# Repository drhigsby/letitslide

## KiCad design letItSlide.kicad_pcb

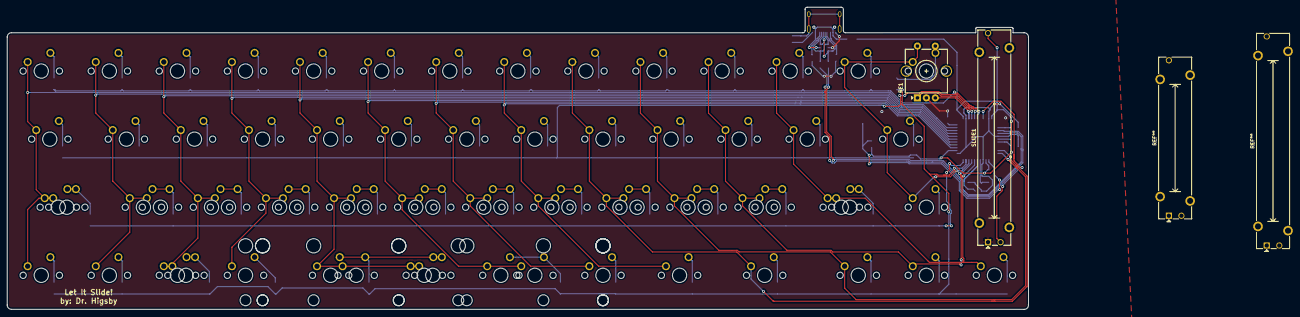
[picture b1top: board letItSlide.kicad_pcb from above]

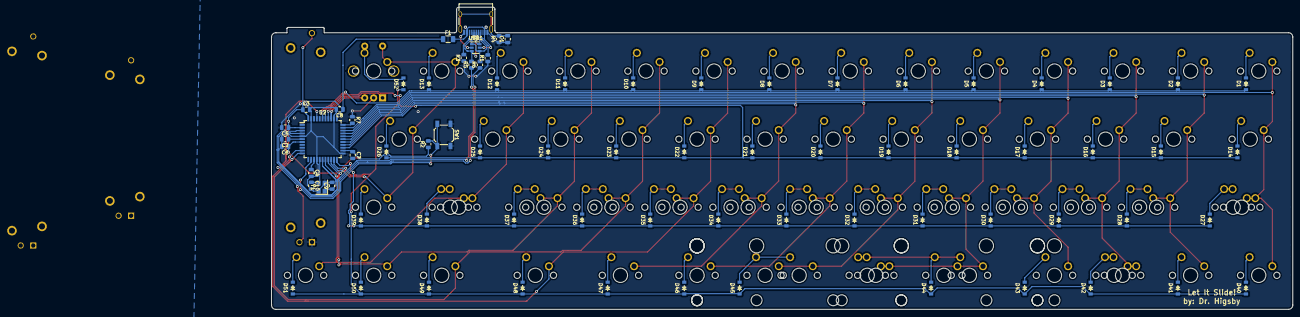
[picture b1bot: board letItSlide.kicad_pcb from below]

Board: 2 copper layers, 285.8 x 84.5 mm, 146 parts (75 on the bottom side), 87 nets.

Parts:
C1: 4.7n; C_0805_2012Metric
C2: 1uF; C_0805_2012Metric
C3, C4, C5, C6, C7: 0.1uF; C_0805_2012Metric
C8: 10uF; C_0805_2012Metric
C9, C10: 22; C_0805_2012Metric
D1, D2, D3, D4, D5, D6, D7, D8, D9, D10, D11, D12, D13, D14, D15, D16, D17, D18, D19, D20, D21, D22, D23, D24, D25, D26, D27, D28, D29, D30, D31, D32, D33, D34, D35, D36, D37, D38, D39, D40, D41, D42, D43, D44, D45, D46, D47, D48, D49, D50, D51, D52: D_Small; D_SOD-123
F1: 500 mA; Fuse_1206_3216Metric
MX1, MX2, MX3, MX4, MX5, MX6, MX7, MX8, MX9, MX10, MX11, MX12, MX13, MX15, MX16, MX17, MX18, MX19, MX20, MX21, MX22, MX23, MX24, MX25, MX28, MX28#2, MX29, MX29#2, MX30, MX30#2, MX31, MX31#2, MX32, MX32#2, MX33, MX33#2, MX34, MX34#2, MX35, MX35#2, MX36, MX36#2, MX37, MX37#2, MX39, MX40, MX41, MX42, MX43, MX46, MX49, MX50, MX51, MX52: MX-NoLED; MXOnly-1U-NoLED
MX14, MX38-1.25u1, MX42-1.25u1, MX47, MX48: MX-NoLED; MXOnly-1.25U-NoLED
MX26, MX27-1.75u1: MX-NoLED; MXOnly-1.75U-NoLED
MX27, MX38: MX-NoLED; MXOnly-1.5U-NoLED
MX44: MX-NoLED; MXOnly-2.25U-ReversedStabilizers-NoLED
MX44-3u1, MX45-3u1: MX-NoLED; MXOnly-3U-ReversedStabilizers-NoLED
MX44-6.25u1: MX-NoLED; MXOnly-6.25U-ReversedStabilizers-NoLED
MX44-6u1: MX-NoLED; MXOnly-6U-Centered-ReversedStabilizers-NoLED
MX45: MX-NoLED; MXOnly-2U-ReversedStabilizers-NoLED
R1, R3: 5.1k; R_0805_2012Metric
R2, R7: 10k; R_0805_2012Metric
R4: 1M; R_0805_2012Metric
R5, R6: 22; R_0805_2012Metric
RE1: Rotary_Encoder_Switch; RotaryEncoder_Alps_EC11E-Switch_Vertical_H20mm_CircularMoun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
SLIDE1: Conn_01x07_Male; Potentiometer_Bourns_PTA4543_Single_Slide
SW1: SW_Push; SW_SPST_SKQG_WithStem
U1: SRV05-4; SOT-23-6
U2: ATmega32U4-AU; TQFP-44_10x10mm_P0.8mm
USB1: USB_C_Receptacle_USB2.0; USB_C_Receptacle_HRO_TYPE-C-31-M-12
Y1: Crystal_GND24_Small; Crystal_SMD_3225-4Pin_3.2x2.5mm

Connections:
+5V: C3.1, C4.1, C5.1, C6.1, C7.1, C8.1, F1.1, R2.1, SLIDE1.3, U2.2, U2.7, U2.14, U2.24, U2.34, U2.44
ANAL_IN: SLIDE1.2, U2.41
D+: R5.2, U1.3, U1.6, USB1.A6, USB1.B6
D-: R6.2, U1.1, U1.4, USB1.A7, USB1.B7
Earth: C1.2, R4.2, USB1.S1
GND: C1.1, C2.2, C3.2, C4.2, C5.2, C6.2, C7.2, C8.2, C9.2, C10.2, R1.1, R3.1, R4.1, R7.1, RE1.C, SLIDE1.1, SW1.1, U1.2, U2.5, U2.15, U2.23, U2.35, U2.43, USB1.A1, USB1.A12, USB1.B1, USB1.B12, Y1.2, Y1.4
MG1: RE1.B, U2.36
MG2: RE1.A, U2.37
unnamed: C2.1, U2.6
unnamed: C9.1, U2.17, Y1.1
unnamed: C10.1, U2.16, Y1.3
unnamed: D1.2, MX1.2
unnamed: D2.2, MX2.2
unnamed: D3.2, MX3.2
unnamed: D4.2, MX4.2
unnamed: D5.2, MX5.2
unnamed: D6.2, MX6.2
unnamed: D7.2, MX7.2
unnamed: D8.2, MX8.2
unnamed: D9.2, MX9.2
unnamed: D10.2, MX10.2
unnamed: D11.2, MX11.2
unnamed: D12.2, MX12.2
unnamed: D13.2, MX13.2
unnamed: D14.2, MX14.2
unnamed: D15.2, MX15.2
unnamed: D16.2, MX16.2
unnamed: D17.2, MX17.2
unnamed: D18.2, MX18.2
unnamed: D19.2, MX19.2
unnamed: D20.2, MX20.2
unnamed: D21.2, MX21.2
unnamed: D22.2, MX22.2
unnamed: D23.2, MX23.2
unnamed: D24.2, MX24.2
unnamed: D25.2, MX25.2
unnamed: D26.2, MX26.2
unnamed: D27.2, MX27.2, MX27-1.75u1.2
unnamed: D28.2, MX28.2, MX28#2.2
unnamed: D29.2, MX29.2, MX29#2.2
unnamed: D30.2, MX30.2, MX30#2.2
unnamed: D31.2, MX31.2, MX31#2.2
unnamed: D32.2, MX32.2, MX32#2.2
unnamed: D33.2, MX33.2, MX33#2.2
unnamed: D34.2, MX34.2, MX34#2.2
unnamed: D35.2, MX35.2, MX35#2.2
unnamed: D36.2, MX36.2, MX36#2.2
unnamed: D37.2, MX37.2, MX37#2.2
unnamed: D38.2, MX38.2, MX38-1.25u1.2
unnamed: D39.2, MX39.2
unnamed: D40.2, MX40.2
unnamed: D41.2, MX41.2
unnamed: D42.2, MX42.2, MX42-1.25u1.2
unnamed: D43.2, MX43.2
unnamed: D44.2, MX44.2, MX44-3u1.2, MX44-6.25u1.2, MX44-6u1.2
unnamed: D45.2, MX45.2, MX45-3u1.2
unnamed: D46.2, MX46.2
unnamed: D47.2, MX47.2
unnamed: D48.2, MX48.2
unnamed: D49.2, MX49.2
unnamed: D50.2, MX50.2
unnamed: D51.2, MX51.2
unnamed: D52.2, MX52.2, RE1.S1
unnamed: R1.2, USB1.A5
unnamed: R2.2, SW1.2, U2.13
unnamed: R3.2, USB1.B5
unnamed: R5.1, U2.4
unnamed: R6.1, U2.3
unnamed: R7.2, U2.33
VCC: F1.2, U1.5, USB1.A4, USB1.A9, USB1.B4, USB1.B9
c1: MX1.1, MX14.1, MX27.1, MX27-1.75u1.1, MX40.1, U2.32
c2: MX2.1, MX15.1, MX28.1, MX28#2.1, MX41.1, U2.31
c3: MX3.1, MX16.1, MX29.1, MX29#2.1, MX42.1, MX42-1.25u1.1, U2.30
c4: MX4.1, MX17.1, MX30.1, MX30#2.1, MX43.1, U2.29
c5: MX5.1, MX18.1, MX31.1, MX31#2.1, MX44.1, MX44-3u1.1, MX44-6.25u1.1, MX44-6u1.1, U2.28
c6: MX6.1, MX19.1, MX32.1, MX32#2.1, MX45.1, MX45-3u1.1, U2.27
c7: MX7.1, MX20.1, MX33.1, MX33#2.1, MX46.1, U2.26
c8: MX8.1, MX21.1, MX34.1, MX34#2.1, MX47.1, U2.25
c9: MX9.1, MX22.1, MX35.1, MX35#2.1, MX48.1, U2.10
c10: MX10.1, MX23.1, MX36.1, MX36#2.1, MX49.1, U2.11
c11: MX11.1, MX24.1, MX37.1, MX37#2.1, MX50.1, U2.19
c12: MX12.1, MX25.1, MX38.1, MX38-1.25u1.1, MX51.1, U2.18
c13: MX13.1, MX26.1, MX39.1, MX52.1, RE1.S2, U2.20
r1: D1.1, D2.1, D3.1, D4.1, D5.1, D6.1, D7.1, D8.1, D9.1, D10.1, D11.1, D12.1, D13.1, U2.39
r2: D14.1, D15.1, D16.1, D17.1, D18.1, D19.1, D20.1, D21.1, D22.1, D23.1, D24.1, D25.1, D26.1, U2.38
r3: D27.1, D28.1, D29.1, D30.1, D31.1, D32.1, D33.1, D34.1, D35.1, D36.1, D37.1, D38.1, D39.1, U2.22
r4: D40.1, D41.1, D42.1, D43.1, D44.1, D45.1, D46.1, D47.1, D48.1, D49.1, D50.1, D51.1, D52.1, U2.21

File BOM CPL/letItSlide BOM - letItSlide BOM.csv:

Comment,Designator,Footprint,LCSC
4.7n,C1,Capacitor_SMD:C_0805_2012Metric,C53987
1uF,C2,Capacitor_SMD:C_0805_2012Metric,C15849
0.1uF,"C3,C4,C5,C6,C7",Capacitor_SMD:C_0805_2012Metric,C14663
10uF,C8,Capacitor_SMD:C_0805_2012Metric,C19702
22pF,"C9,C10",Capacitor_SMD:C_0805_2012Metric,C1653
D_Small,"D1,D2,D3,D4,D5,D6,D7,D8,D9,D10,D11,D12,D13,D14,D15,D16,D17,D18,D19,D20,D21,D22,D23,D24,D25,D26,D27,D28,D29,D30,D31,D32,D33,D34,D35,D36,D37,D38,D39,D40,D41,D42,D43,D44,D45,D46,D47,D48,D49,D50,D51,D52",Diode_SMD:D_SOD-123,C81598
500 mA,F1,Fuse:Fuse_1206_3216Metric,C70076
5.1k,"R1,R3",Resistor_SMD:R_0805_2012Metric,C27834
1M,R4,Resistor_SMD:R_0805_2012Metric,C22935
22,"R5,R6",Resistor_SMD:R_0805_2012Metric,C17561
10k,"R2,R7",Resistor_SMD:R_0805_2012Metric,C17414
SW_Push,SW1,Button_Switch_SMD:SW_SPST_SKQG_WithStem,C318884
SRV05-4,U1,Package_TO_SOT_SMD:SOT-23-6,C85364
ATmega32U4-AU,U2,Package_QFP:TQFP-44_10x10mm_P0.8mm,C44854
USB_C_Receptacle_USB2.0,USB1,Connector_USB:USB_C_Receptacle_HRO_TYPE-C-31-M-12,C165948
Crystal_GND24_Small,Y1,Crystal:Crystal_SMD_3225-4Pin_3.2x2.5mm,C13738

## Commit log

2022-03-28 minor update
    includes testing .hex
2022-04-28 updating repo
    cleaning it up a bit
2022-05-08 This message brought to you by an extra strong 8oz Stumptown americano
2022-06-11 [fix][feature] Fixed matrix scan for slider to properly isolate kb function from user function. Added custom keycode to toggle volume and other custom keycode behavior between Win & Mac.
2022-06-12 [fix] Reduction of complexity. No need for timer.
